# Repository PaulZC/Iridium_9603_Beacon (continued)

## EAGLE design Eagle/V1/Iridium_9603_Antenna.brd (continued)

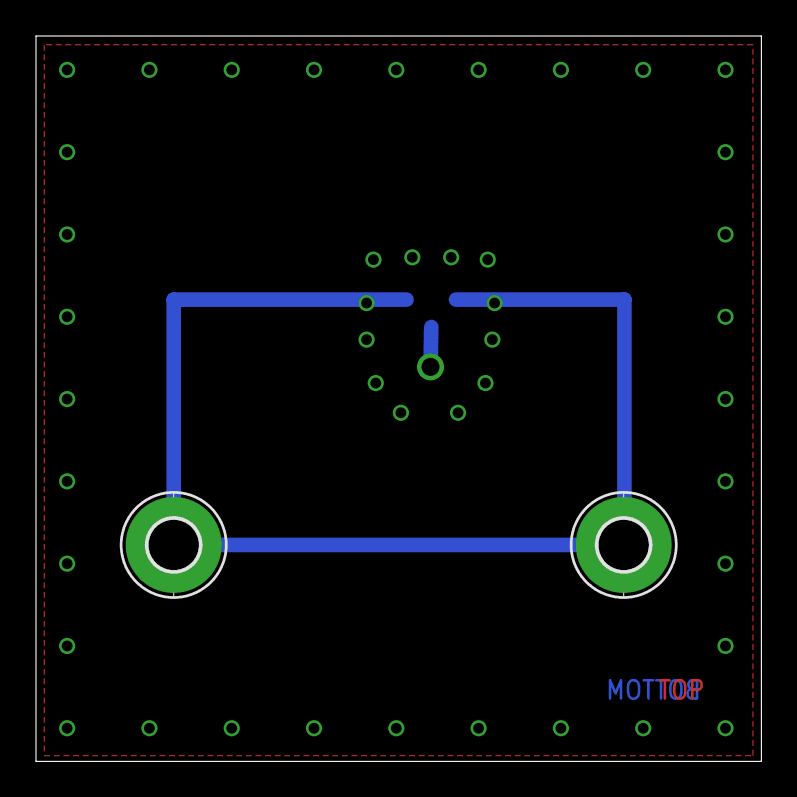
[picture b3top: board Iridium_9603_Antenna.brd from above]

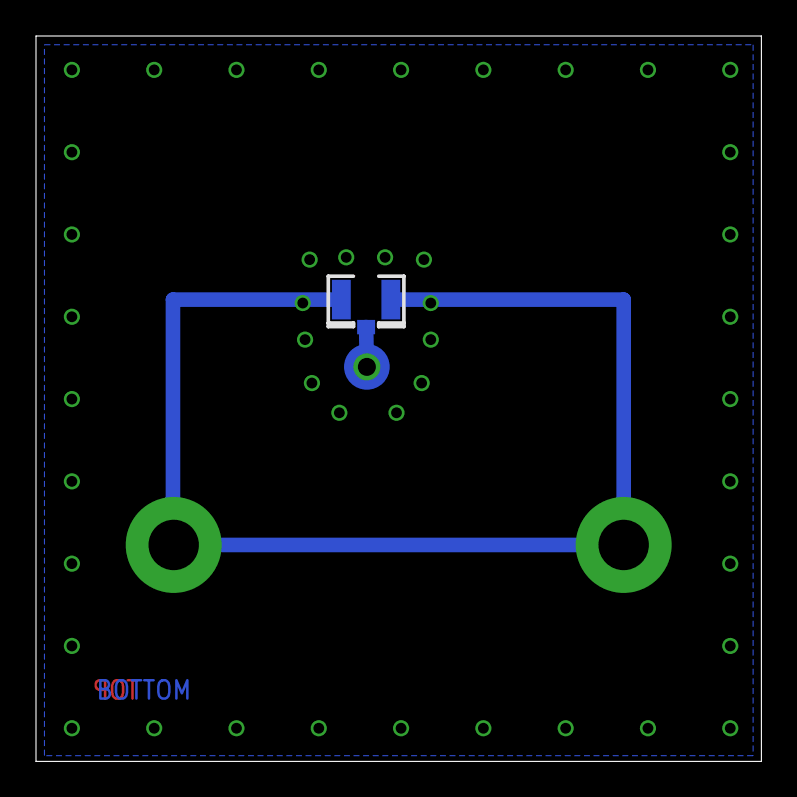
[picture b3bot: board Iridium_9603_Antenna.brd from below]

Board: 2 copper layers, 40.3 x 40.3 mm, 4 parts (2 on the bottom side), 2 nets.

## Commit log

2016-10-06 :circus_tent: Added .gitattributes & .gitignore files
2016-10-06 First Release
2016-12-03 Substantial update following completion and test of the first PCB
2017-03-18 Substantial update following UBSEDS22I test flight
2017-04-16 Updates for Version 3
    Major update:
    Beacon can be operated from solar power
    GPS (GNSS) data now provided by u-blox SAM-M8Q
2017-04-17 Updates of the readme, V3 pdf and the UBSEDS22I kml files
2017-04-17 Small bug fix: converting iterationCounter to a string
2017-04-17 Added a paste mask for V3 PCB
    The paste mask fiducials are oversized by 111% so will be the correct
    size when the mask apertures are undersized by 10%
2017-04-17 Improved the ground plane under the SAM-M8Q
2017-04-18 Final tweaks before sending V3 for manufacture
2017-09-16 Substantial update for V3
    Substantial update to match V3 of the PCB: now includes u-blox SAM-M8Q
    GNSS and the option of solar power
2017-09-16 Tidying up...
2017-09-16 Updates to match V3 PCB
2017-09-16 Updating LEARN.md (work in progress)
2017-09-16 Updates for V3
2017-09-16 Updated LEARN.md for V3
2017-09-17 Added cable lengths for inclined solar panels
2017-12-25 Updates for V2.0 of IridiumSBD
2017-12-27 Updated supercapacitor charger current draw.
2017-12-27 Read pressure twice to avoid first erroneous value
2018-01-01 Added V4 - Work In Progress!
2018-01-03 Improvements to zoom level processing
2018-01-03 Added right-click: copies click location to clipboard
2018-01-04 Tested on Raspberry Pi. Updated zoom look-up table.
2018-01-05 Corrected scale multiplier
2018-01-08 Major update. Base.py now tracks up to 8 beacons.
2018-01-09 Added beacon location pull-down menu
2018-01-10 Now includes pull-down menu for the base
2018-01-27 Minor updates
2018-02-01 Important updates to TinyGPS data processing
2018-02-02 Beacon Base can now use offline files (from Tiler)
2018-02-04 Updates following tests through RockBLOCK gateway
2018-02-04 Added split pads for supercapacitor charge current
2018-02-04 Added a comma after the destination RockBLOCK address
2018-02-04 Minor tweaks
2018-02-07 Initial update for V4 - still work in progress
2018-02-08 Updated the PCB images
2018-02-11 Included full details of RockBLOCK gateway messaging
2018-02-11 Added results of the cold test
2018-02-11 Added an image of the split pads
2018-02-11 Added an image of the 10F supercapacitors
2018-02-18 Added an option to power down the base 9603N
2018-03-06 Updated the BOM
2018-03-20 Substantial update
    BEACON_INTERVAL is now stored in non-volatile memory and can be updated
    via a Mobile Terminated SBD message sent from RockBLOCK Operations or
    Iridium_Beacon_Base.
2018-03-20 Added a proper acknowledgement for CM's FlashStorage
2018-03-30 Added Python extras
    Added extra Python utilities to stitch the .bin SBD attachments together
    and convert them into KML format for Google Earth
2018-03-30 Added install details for simplekml
2018-04-11 Added a delay to make NeoPixel start reliably
2018-05-18 Major update for V5
2018-05-19 Added the Gerber files
2018-05-19 Corrected the quotes
2018-05-27 Added support for relay pulses
    Added support for relay pulses (to trigger e.g. a cut-down unit)
2018-05-27 Clarified the pulse durations
2018-05-28 Updated the Base code
    Updated the Base code:
    The relay pins are initialised - but not used.
    The Enable_9603N pin is initialised and used.
2018-05-28 Corrected the links to the V5 code
2018-06-09 Remote configuration of RockBLOCK messaging
    Previously it was only possible to enable RockBLOCK Gateway message forwarding by editing the Arduino code. This can now be done by sending Mobile Terminated messages through RockBLOCK Operations.
2018-06-09 Added a hyperlink
2018-06-09 Added extra info about the Tiler
2018-07-07 Updated Iridium_Beacon_Base.py
    Updated Iridium_Beacon_Base.py: improved the blocking during Iridium communication. Added support for RGB tri-colour LED.
2018-07-14 Improvements to Beacon_Base
2018-08-04 Important Bugfix!
    Corrected a bug where the code would ignore an RBDESTINATION of 0 (i.e. message forwarding could not be disabled once enabled)
2018-09-15 Updated RockBLOCK.md
2018-09-15 Corrected RockBLOCK.md
2018-09-24 Added support for the new radio board
2018-09-26 Updated RockBLOCK Mapper
    Updated RockBLOCK Mapper with some of the features of Beacon Base. Code now blocks much less frequently.
2018-10-06 Small updates to the Python code
2018-10-16 Updated the Tiler
    Now defaults to 'hybrid' map tiles. Tile filenames now use 3 decimal places for lat and lon.
2018-10-17 Added the vector graphics
2018-12-08 Added a photo of the epoxy
2018-12-08 Added ..._CSV_to_KML_RockBLOCK.py
    Added Iridium_Beacon_DateTime_CSV_to_KML_RockBLOCK.py to the Python directory
2018-12-11 Added oauth2client to the required libraries
2019-01-17 Corrected the zero width polygons
    Corrected the zero width polygons in the micro USB connector that were causing problems for OSH Park. Thanks go to Paul Loewen @ usask.ca
2019-01-26 Added the stl and scad files for the covers
2019-02-10 Improved the Mapper file sorting using Mark Byers' sorted_nicely
2019-03-18 Updated vbat and pgood functions
    Updated get_vbat and pgood_count so they are the same as the solar beacon
2019-04-01 Added the habhub habitat uploader
2019-04-10 Added the citation
2019-05-06 Minor improvements
2019-09-22 Corrected the Mapper indentation
2020-03-08 Python3, oauthlib and PyQt5 updates
2020-03-08 Corrected the SCOPES
